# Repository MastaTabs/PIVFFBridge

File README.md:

# PIV FFBridge

Bought a snapped off PicassoIV and don't want to use cables to attach the video slot connector?
Then PIV FFBridge comes to the rescue.
It also integrates the functionality of the CD-Mix that not many people know it exists.
This way, you can listen to CD and Amiga audio through the PIV audio output at the same time.

The design is proven and working good. It was created from the original schematics and PCB layout.

### License
The "PIV FFBridge" documentation, including the design itself, is copyright © MastaTabs (Tobias Seiler) 2020.

"PIV FFBridge" is Open Hardware licensed under the CERN OHL v. 1.2.

You may redistribute and modify this documentation under the terms of the CERN OHL v.1.2. This documentation is distributed as is and WITHOUT ANY EXPRESS OR IMPLIED WARRANTIES whatsoever with respect to its functionality, operability or use, including, without limitation, any implied warranties OF MERCHANTABILITY, SATISFACTORY QUALITY, FITNESS FOR A PARTICULAR PURPOSE or infringement. We expressly disclaim any liability whatsoever for any direct, indirect, consequential, incidental or special damages, including, without limitation, lost revenues, lost profits, losses resulting from business interruption or loss of data, regardless of the form of action or legal theory under which the liability may be asserted, even if advised of the possibility or likelihood of such damages.

A copy of the full license is included in file LICENSE.pdf, please refer to it for applicable conditions. In order to properly deal with its terms, please see file LICENSE_HOWTO.pdf.

The contact points for information about manufactured Products (see section 4.2) are listed in file PRODUCT.md.

Any modifications made by Licensees (see section 3.4.b) shall be recorded in file CHANGES.md.

The Documentation Location of the original project is https://github.com/MastaTabs/PIVFFBridge.

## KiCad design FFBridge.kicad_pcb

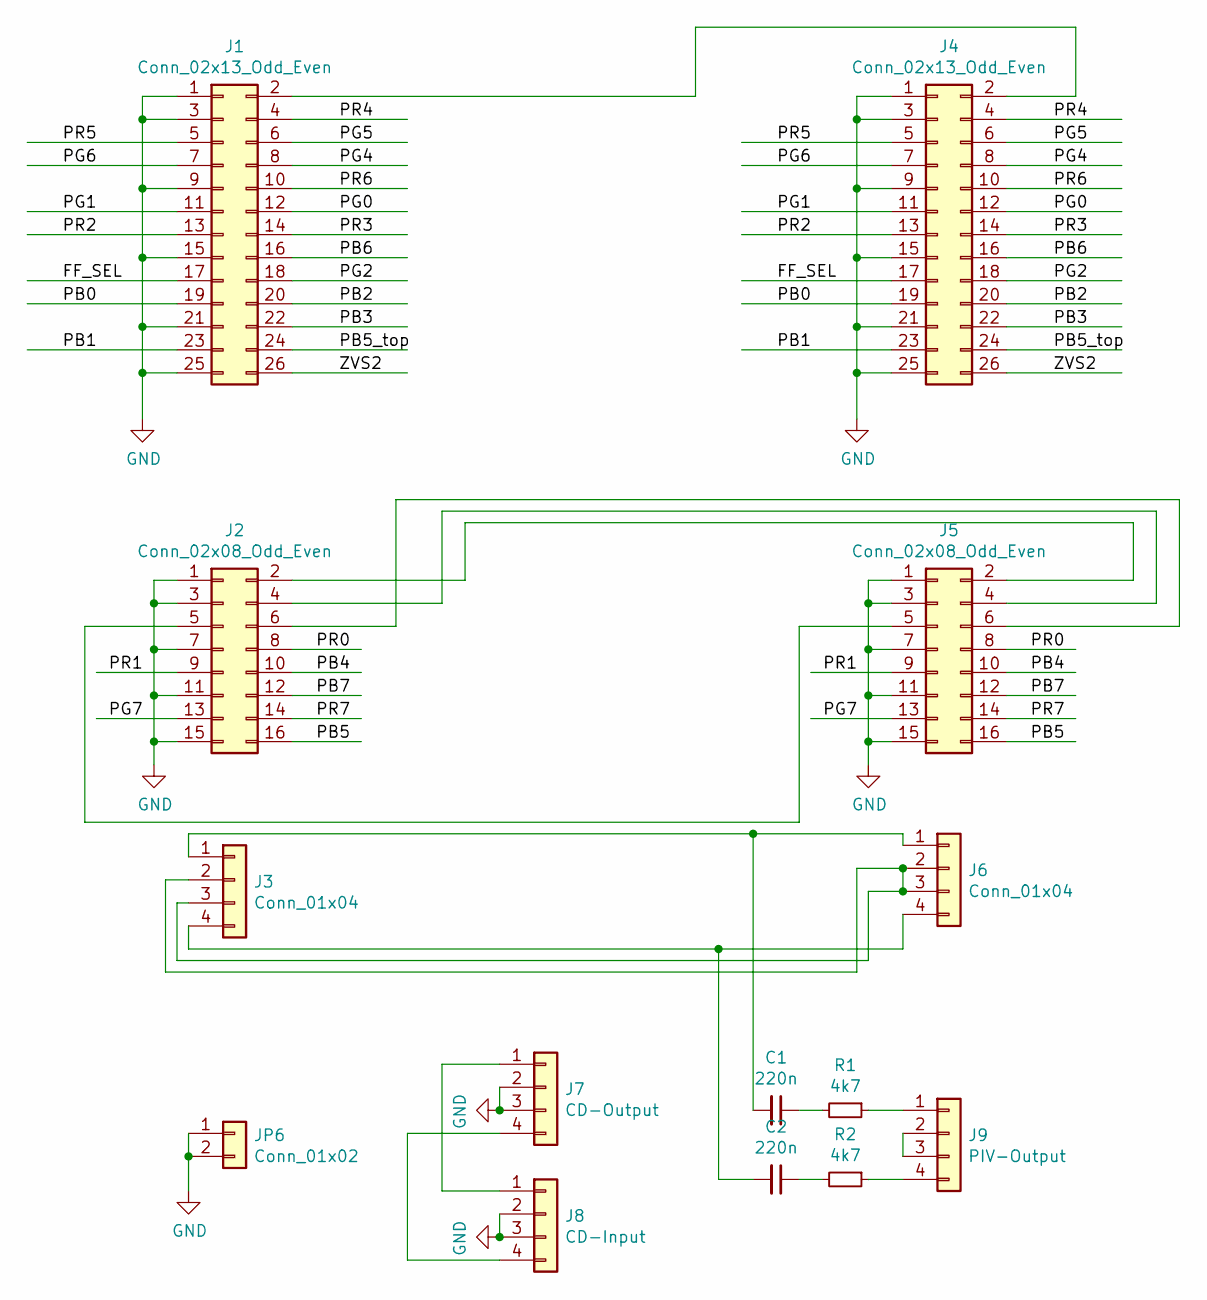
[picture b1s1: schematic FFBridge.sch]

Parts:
C1, C2: 220n; C_0805_HandSoldering
J1, J4: Conn_02x13_Odd_Even; Pin_Header_Straight_2x13_Pitch2.54mm
J2, J5: Conn_02x08_Odd_Even; Pin_Header_Straight_2x08_Pitch2.54mm
J3, J6: Conn_01x04; Pin_Header_Straight_1x04_Pitch2.54mm
J7: CD-Output; Pin_Header_Straight_1x04_Pitch2.54mm
J8: CD-Input; Pin_Header_Angled_1x04_Pitch2.54mm
J9: PIV-Output; Pin_Header_Straight_1x04_Pitch2.54mm
JP6: Conn_01x02; Pin_Header_Straight_1x02_Pitch2.54mm
R1, R2: 4k7; R_0805_HandSoldering

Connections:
/FF_SEL: J1.17, J4.17
/PB0: J1.19, J4.19
/PB1: J1.23, J4.23
/PB2: J1.20, J4.20
/PB3: J1.22, J4.22
/PB4: J2.10, J5.10
/PB5: J2.16, J5.16
/PB5_top: J1.24, J4.24
/PB6: J1.16, J4.16
/PB7: J2.12, J5.12
/PG0: J1.12, J4.12
/PG1: J1.11, J4.11
/PG2: J1.18, J4.18
/PG4: J1.8, J4.8
/PG5: J1.6, J4.6
/PG6: J1.7, J4.7
/PG7: J2.13, J5.13
/PR0: J2.8, J5.8
/PR1: J2.9, J5.9
/PR2: J1.13, J4.13
/PR3: J1.14, J4.14
/PR4: J1.4, J4.4
/PR5: J1.5, J4.5
/PR6: J1.10, J4.10
/PR7: J2.14, J5.14
/ZVS2: J1.26, J4.26
GND: J1.1, J1.3, J1.9, J1.15, J1.21, J1.25, J2.1, J2.3, J2.7, J2.11, J2.15, J4.1, J4.3, J4.9, J4.15, J4.21, J4.25, J5.1, J5.3, J5.7, J5.11, J5.15, J7.2, J7.3, J8.2, J8.3, JP6.1, JP6.2
unnamed: C1.1, R1.2
unnamed: C1.2, J3.1, J6.1
unnamed: C2.1, R2.2
unnamed: C2.2, J3.4, J6.4
unnamed: J1.2, J4.2
unnamed: J2.2, J5.2
unnamed: J2.4, J5.4
unnamed: J2.5, J5.5
unnamed: J2.6, J5.6
unnamed: J3.2, J3.3, J6.2, J6.3
unnamed: J7.1, J8.1
unnamed: J7.4, J8.4
unnamed: J9.1, R1.1
unnamed: J9.2, J9.3
unnamed: J9.4, R2.1

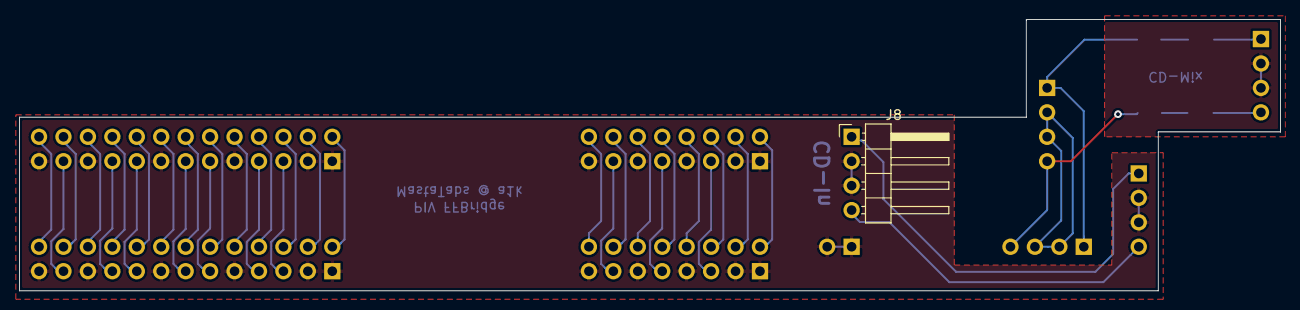
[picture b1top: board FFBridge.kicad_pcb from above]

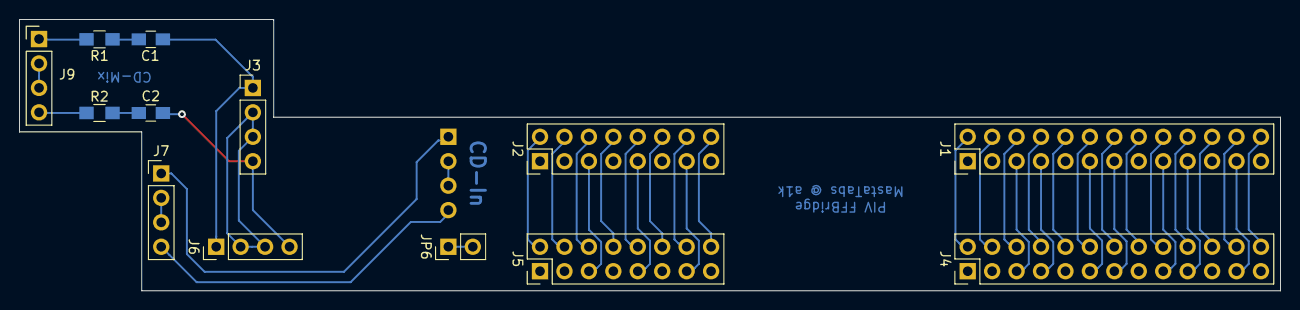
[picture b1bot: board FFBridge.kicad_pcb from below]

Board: 2 copper layers, 131.1 x 28.2 mm, 14 parts (13 on the bottom side), 42 nets.

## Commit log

2020-05-29 cleanup
2020-05-29 link correction
2020-05-30 add License pdf's
2020-05-30 added BOM
